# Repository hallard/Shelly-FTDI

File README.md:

# Shelly FTDI programmer board

This board is used to flash Shelly device with classic 3.3V FTDI USB Serial. 

It's just a kind of wiring wrapper.

# Detailed Description

Look at the schematics for more informations.

# Schematic  

# Boards  

&nbsp;

So you can order boards on [oshpark](https://oshpark.com).

- [V1.0](https://oshpark.com/shared_projects/iro7okxZ)

# BOM

Nothing fancy, just some 2.54mm and 1.27mm headers and 2 B3U-1000P like buttons

# License

This work is licensed under a Creative Commons Attribution-NonCommercial 4.0 International [license](https://creativecommons.org/licenses/by-nc/4.0)

# Misc

See news and other projects on my [blog][1] 

[1]: https://hallard.me

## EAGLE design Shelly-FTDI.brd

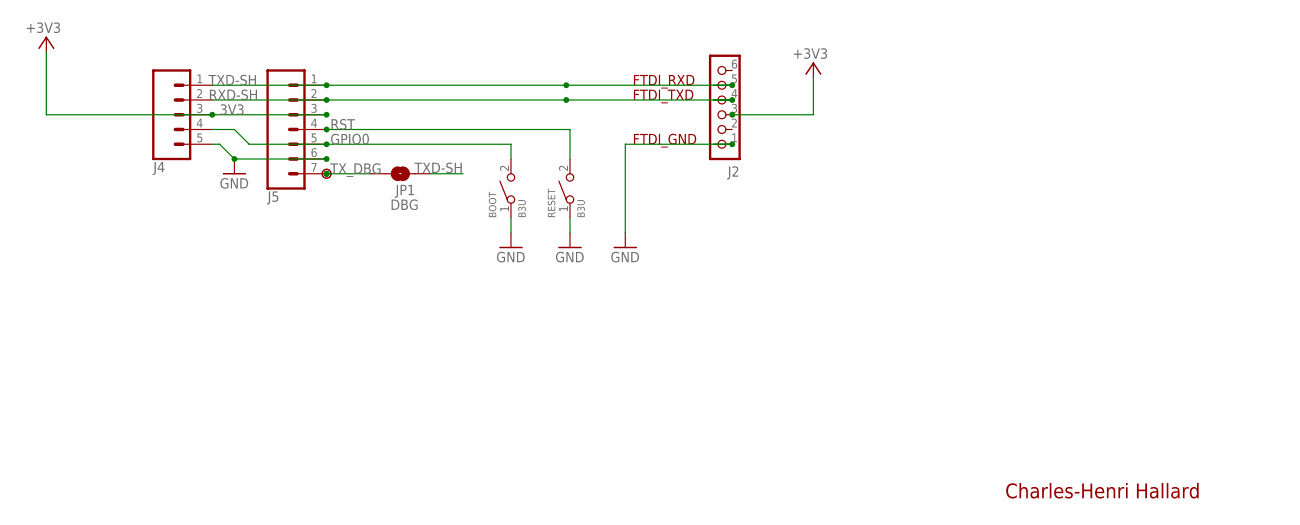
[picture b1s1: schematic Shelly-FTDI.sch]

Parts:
BOOT: B3U; SW2-2.6-3.0X2.5X1.2+0.4MM
J2: CON_HEADER_1X06-PTH; M1X6
J4: CONN_051.27MM; 1X05_1.27MM
J5: CONN_071.27; 1X07_1.27MM
JP1: DBG; PAD-JUMPER-2-NO_NO_SILK
P1: PADSMALL; PAD-SMALL
RESET: B3U; SW2-2.6-3.0X2.5X1.2+0.4MM

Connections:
3V3: J2.3, J4.3, J5.3
GND: BOOT.1, J2.1, J4.5, J5.6, RESET.1
GPIO0: BOOT.2, J4.4, J5.5
RST: J5.4, RESET.2
RXD-SH: J2.4, J4.2, J5.2
TXD-SH: J2.5, J4.1, J5.1, JP1.1
TX_DBG: J5.7, JP1.2, P1.1

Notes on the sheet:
Charles-Henri Hallard
FTDI_RXD
FTDI_TXD
FTDI_GND

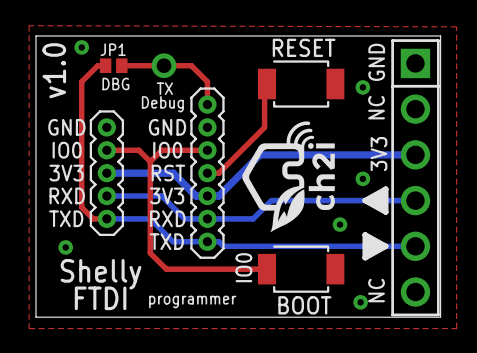
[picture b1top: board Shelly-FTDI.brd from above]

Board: 2 copper layers, 22.5 x 15.6 mm, 9 parts (1 on the bottom side), 7 nets.

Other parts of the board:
U$1, U$2: LOGO_C2I_015

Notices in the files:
parts and their libraries:
SparkFun-Connectors: Licensing: Creative Commons ShareAlike 4.0 International - https://creativecommons.org/licenses/by-sa/4.0
